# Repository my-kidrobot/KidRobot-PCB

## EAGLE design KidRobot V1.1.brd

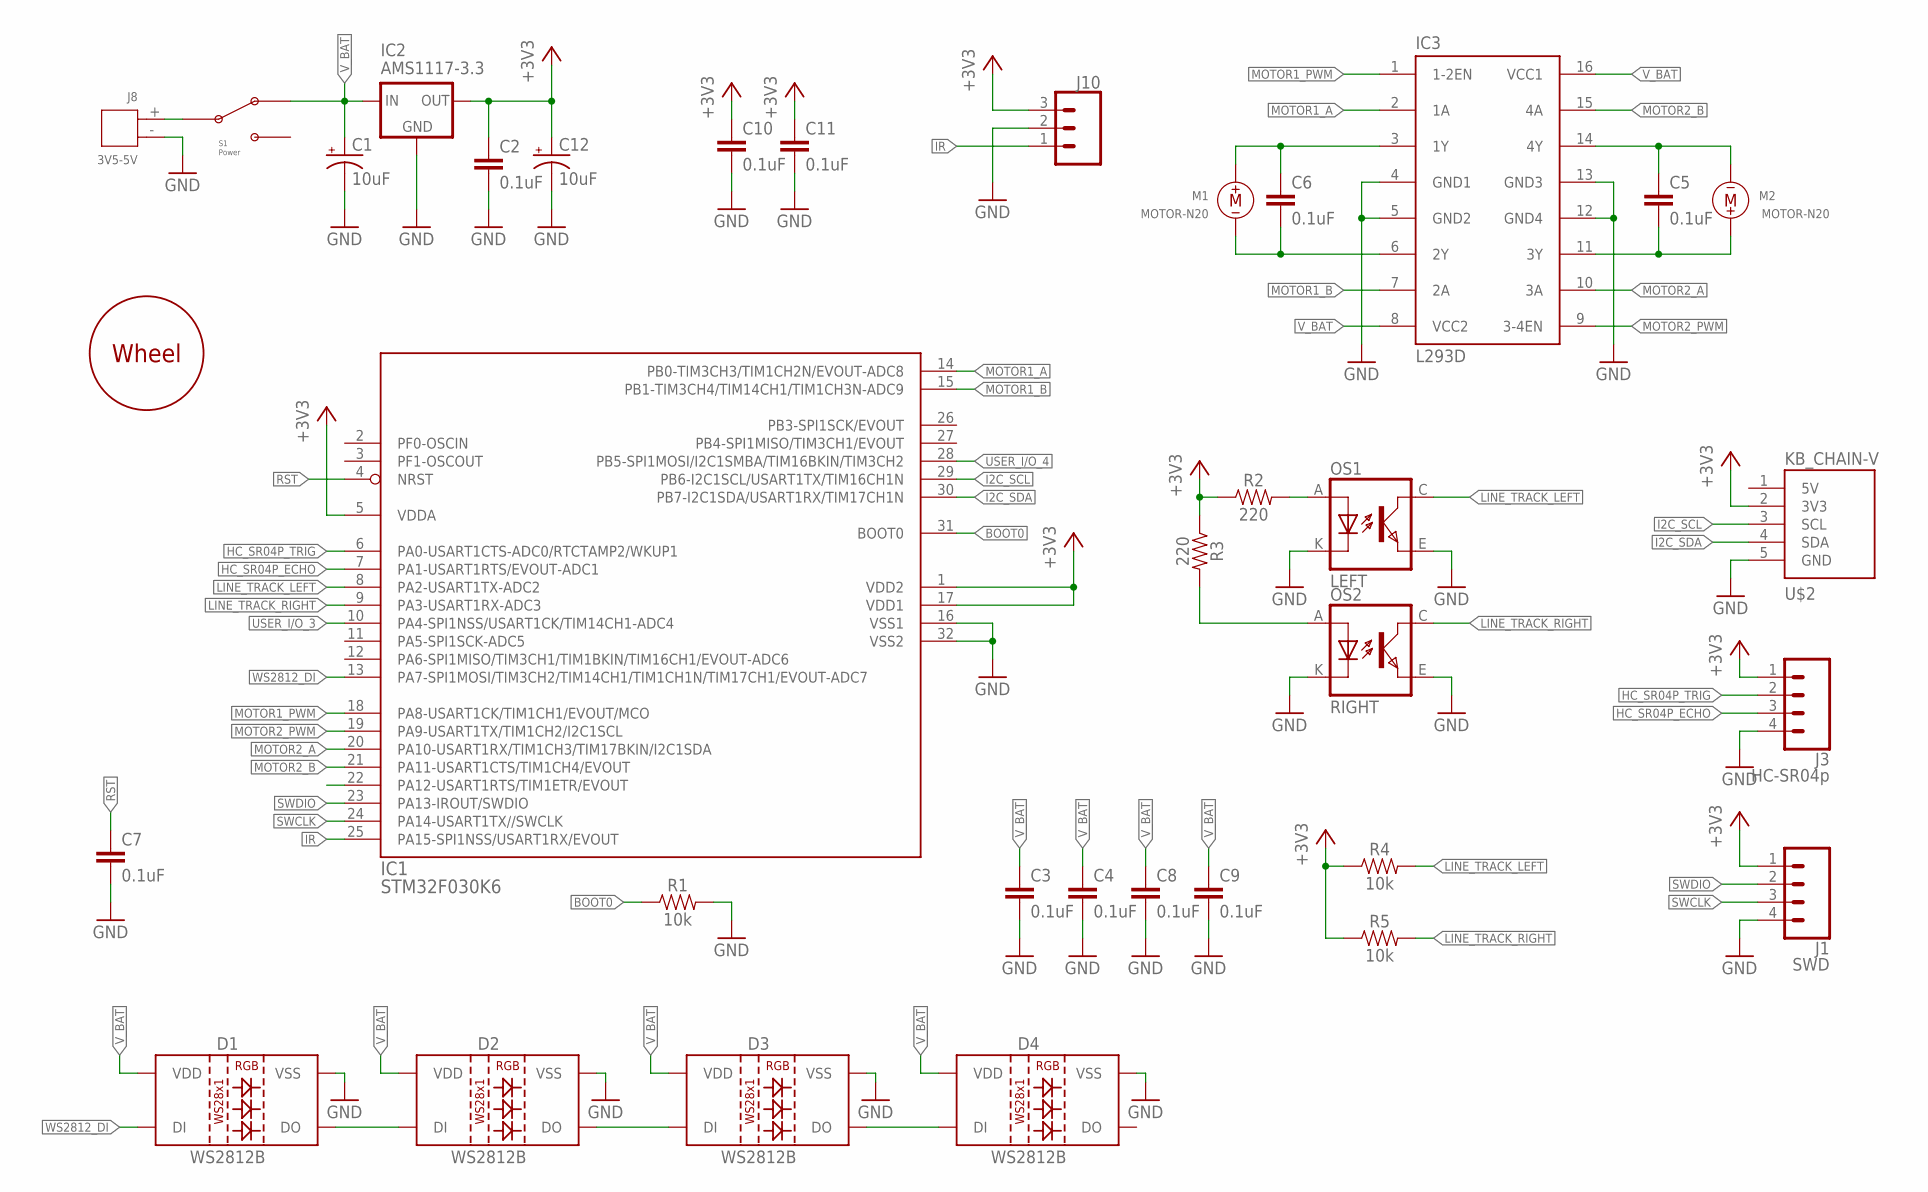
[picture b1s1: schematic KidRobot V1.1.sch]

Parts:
C1, C12: 10uF; CPOL-RADIAL-2.5MM-5MM
C2, C3, C4, C5, C6, C7, C8, C9, C10, C11: 0.1uF; 0603
D1, D2, D3, D4: WS2812B
IC1: STM32F030K6; LQFP32
IC2: AMS1117-3.3; SOT223
IC3: L293D; DIL16
J1: SWD; 1X04
J3: HC-SR04p; 1X04
J8: 3V5-5V; H2-2.0-6X4.5MM
J10: IR Receiver; 1X03
M1, M2: MOTOR-N20; MOTOR-GEAR-N20
OS1: LEFT; TCRT5000
OS2: RIGHT; TCRT5000
R1, R4, R5: 10k; 0603
R2, R3: 220; 0603
S1: Power; SLIDESWITCHES-13X5.5MM
U$1: WHEEL
U$2: KB_CHAIN-V; JST5PIN-V

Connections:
+3V3: C2.1, C10.1, C11.1, C12.1 (+), IC1.1 (VDD2), IC1.5 (VDDA), IC1.17 (VDD1), IC2.2 (OUT), J1.1, J3.1, J10.3, R2.1, R3.1, R4.1, R5.1, U$2.2 (3V3)
BOOT0: IC1.31 (BOOT0), R1.1
GND: C1.2 (-), C2.2, C3.2, C4.2, C7.2, C8.2, C9.2, C10.2, C11.2, C12.2 (-), D1.3 (VSS), D2.3 (VSS), D3.3 (VSS), D4.3 (VSS), IC1.16 (VSS1), IC1.32 (VSS2), IC2.1 (GND), IC3.4 (GND1), IC3.5 (GND2), IC3.12 (GND4), IC3.13 (GND3), J1.4, J3.4, J8.-, J10.2, OS1.E (EMITTER), OS1.K (CATHODE), OS2.E (EMITTER), OS2.K (CATHODE), R1.2, U$2.5 (GND)
HC_SR04P_ECHO: IC1.7 (PA1-USART1RTS/EVOUT-ADC1), J3.3
HC_SR04P_TRIG: IC1.6 (PA0-USART1CTS-ADC0/RTCTAMP2/WKUP1), J3.2
I2C_SCL: IC1.29 (PB6-I2C1SCL/USART1TX/TIM16CH1N), U$2.3 (SCL)
I2C_SDA: IC1.30 (PB7-I2C1SDA/USART1RX/TIM17CH1N), U$2.4 (SDA)
IR: IC1.25 (PA15-SPI1NSS/USART1RX/EVOUT), J10.1
LINE_TRACK_LEFT: IC1.8 (PA2-USART1TX-ADC2), OS1.C (COLLECTOR), R4.2
LINE_TRACK_RIGHT: IC1.9 (PA3-USART1RX-ADC3), OS2.C (COLLECTOR), R5.2
MOTOR1_A: IC1.14 (PB0-TIM3CH3/TIM1CH2N/EVOUT-ADC8), IC3.2 (1A)
MOTOR1_B: IC1.15 (PB1-TIM3CH4/TIM14CH1/TIM1CH3N-ADC9), IC3.7 (2A)
MOTOR1_PWM: IC1.18 (PA8-USART1CK/TIM1CH1/EVOUT/MCO), IC3.1 (1-2EN)
MOTOR2_A: IC1.20 (PA10-USART1RX/TIM1CH3/TIM17BKIN/I2C1SDA), IC3.10 (3A)
MOTOR2_B: IC1.21 (PA11-USART1CTS/TIM1CH4/EVOUT), IC3.15 (4A)
MOTOR2_PWM: IC1.19 (PA9-USART1TX/TIM1CH2/I2C1SCL), IC3.9 (3-4EN)
unnamed: D1.2 (DO), D2.4 (DI)
unnamed: C6.1, IC3.3 (1Y), M1.+
unnamed: C6.2, IC3.6 (2Y), M1.-
unnamed: C5.1, IC3.14 (4Y), M2.-
unnamed: C5.2, IC3.11 (3Y), M2.+
unnamed: D2.2 (DO), D3.4 (DI)
unnamed: J8.+, S1.2
unnamed: OS2.A (ANODE), R3.2
unnamed: OS1.A (ANODE), R2.2
unnamed: D3.2 (DO), D4.4 (DI)
RST: C7.1, IC1.4 (NRST)
SWCLK: IC1.24 (PA14-USART1TX//SWCLK), J1.3
SWDIO: IC1.23 (PA13-IROUT/SWDIO), J1.2
USER_I/O_3: IC1.10 (PA4-SPI1NSS/USART1CK/TIM14CH1-ADC4)
USER_I/O_4: IC1.28 (PB5-SPI1MOSI/I2C1SMBA/TIM16BKIN/TIM3CH2)
V_BAT: C1.1 (+), C3.1, C4.1, C8.1, C9.1, D1.1 (VDD), D2.1 (VDD), D3.1 (VDD), D4.1 (VDD), IC2.3 (IN), IC3.8 (VCC2), IC3.16 (VCC1), S1.1
WS2812_DI: D1.4 (DI), IC1.13 (PA7-SPI1MOSI/TIM3CH2/TIM14CH1/TIM1CH1N/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)

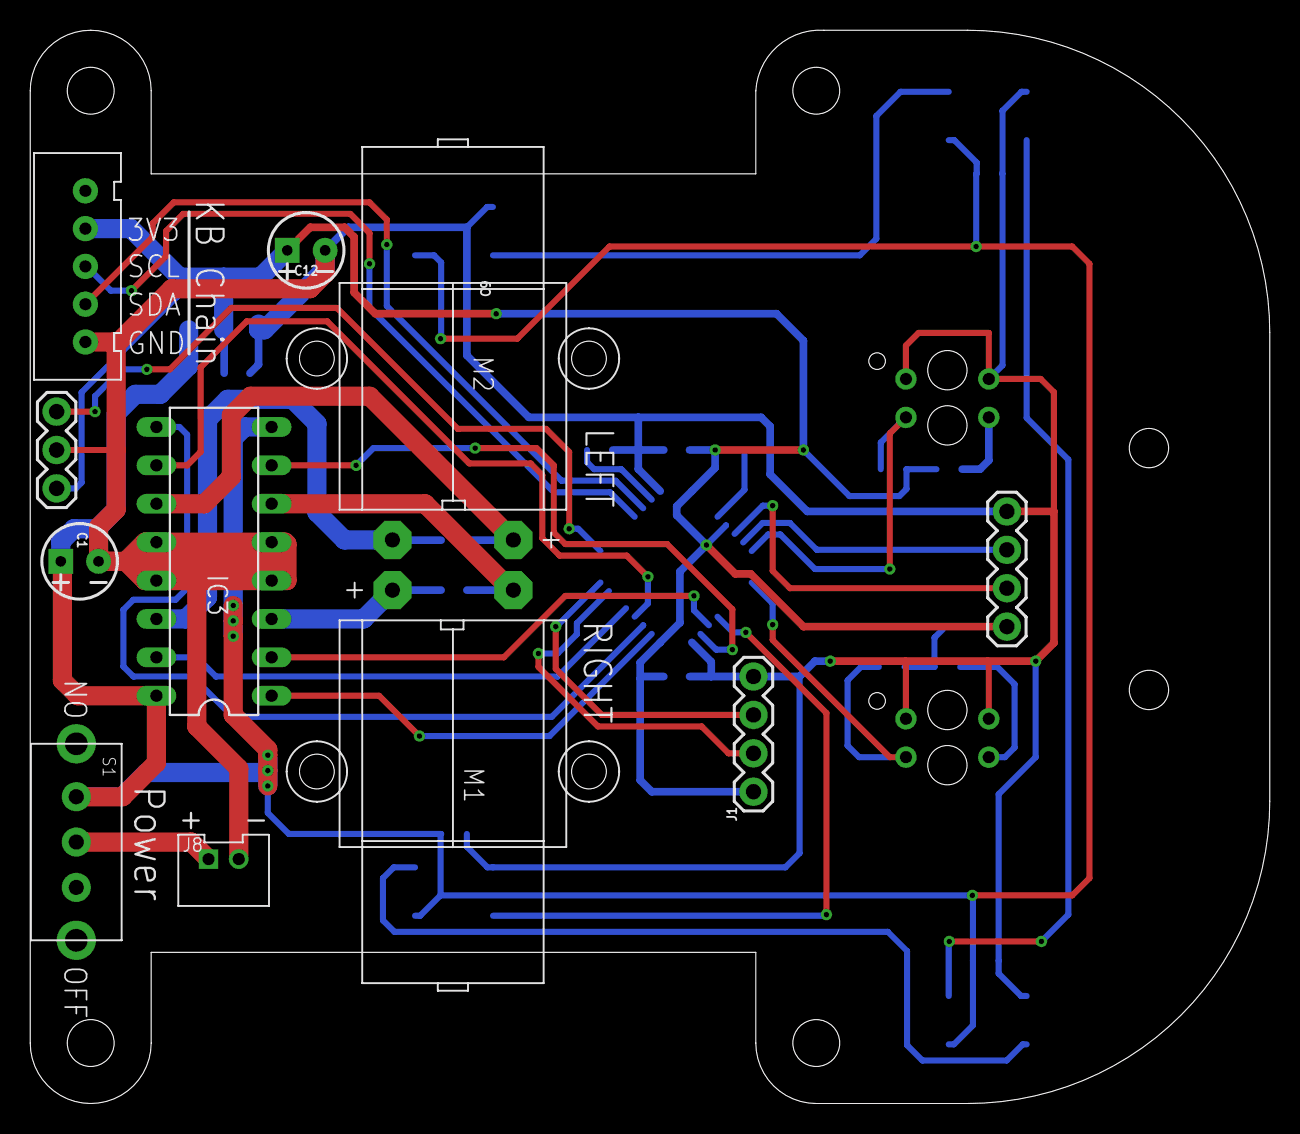
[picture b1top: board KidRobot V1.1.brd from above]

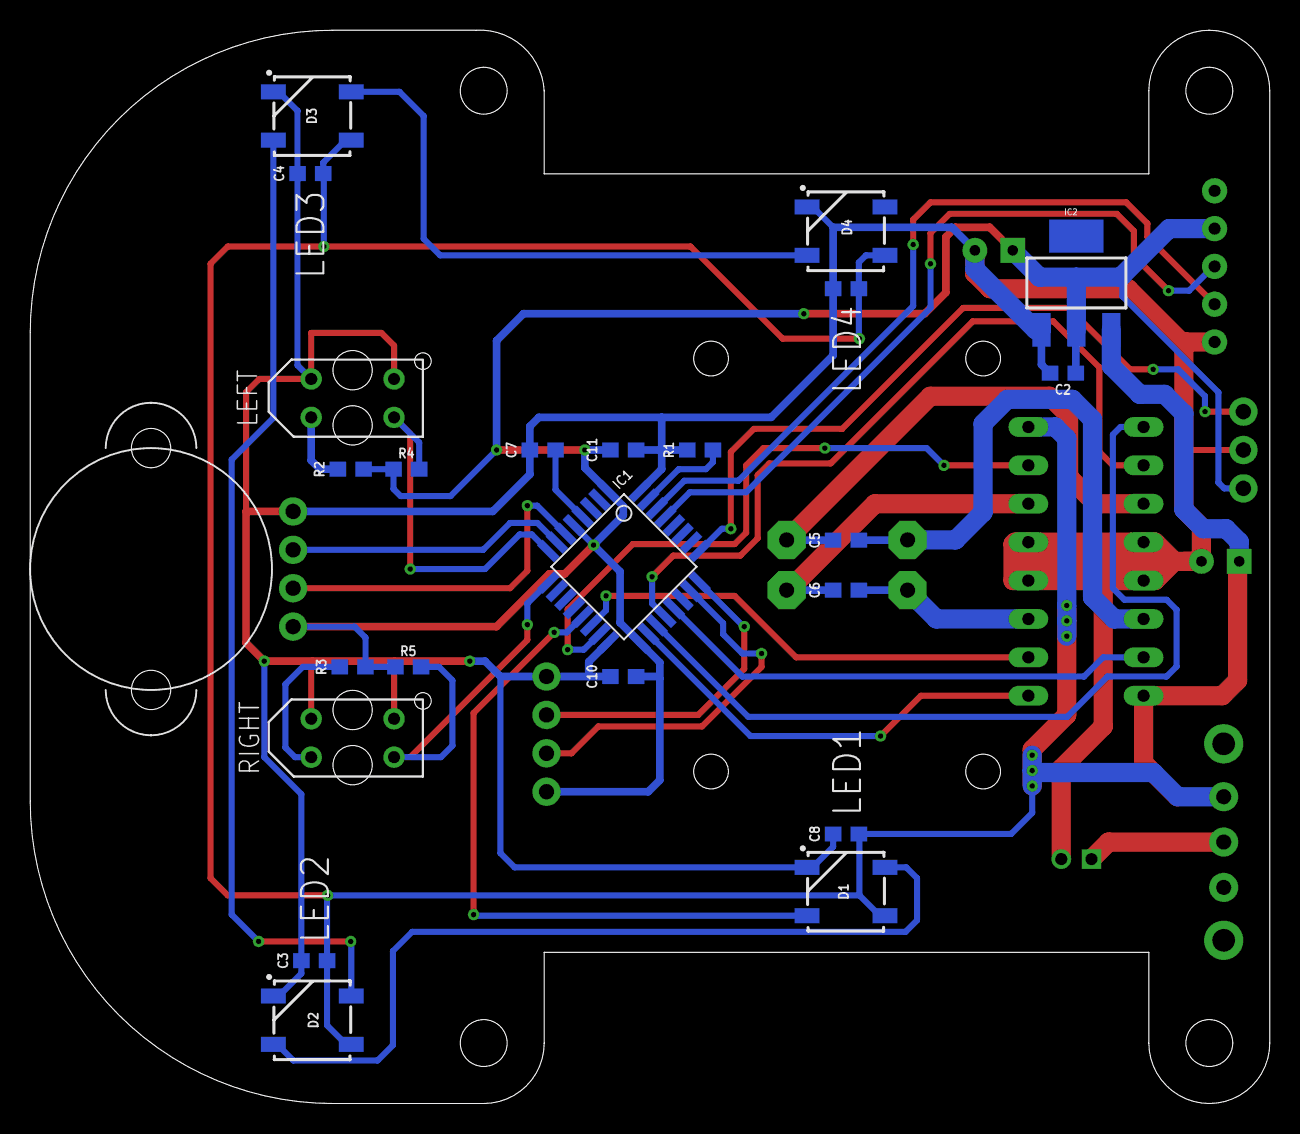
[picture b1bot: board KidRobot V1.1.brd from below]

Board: 2 copper layers, 82.0 x 71.0 mm, 35 parts (23 on the bottom side), 31 nets.

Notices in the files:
parts and their libraries:
SparkFun-IC-Power: Licensing: Creative Commons ShareAlike 4.0 International - https://creativecommons.org/licenses/by-sa/4.0
